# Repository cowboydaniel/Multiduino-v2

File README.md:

# Multiduino v2

**by Outback Electronics** — Arduino-Compatible Development Board

---

## Overview

The Multiduino v2 is an Arduino Uno-compatible development board designed for projects that need more than a standard Uno can offer. It uses the ATmega328PB processor and ATmega16U2 USB bridge — the same architecture as the official Arduino Uno R3, with a drop-in compatible (but enhanced) variant of the Uno's ATmega328P.

On top of the standard Uno feature set, the Multiduino v2 adds a substantial suite of on-board hardware: extra RAM and non-volatile storage, a precision real-time clock, a humidity and temperature sensor, a microSD card slot, and a switchable 3.3V power rail. Everything is ready to use without any external modules or wiring.

**Two ways to use this board:**

**Arduino Uno compatible mode** — Select **Arduino Uno** as your board in the Arduino IDE and the Multiduino v2 works immediately with standard Arduino libraries. This is the quickest way to get started and is fully supported. Compatible libraries for all on-board peripherals are available through the Arduino Library Manager.

**Multiduino core** — Outback Electronics provides a custom Arduino core specifically designed for this board. It includes tailored libraries for every on-board peripheral that expose hardware-specific functionality not possible with generic libraries. The Multiduino core is recommended for any project making full use of the board's hardware. See the [Multiduino Core repository](https://github.com/cowboydaniel/outback-arduino-avr) for installation instructions.

---

## What's On The Board

### Processor
The ATmega328PB is an enhanced version of the ATmega328P found in the official Arduino Uno R3. It is fully backward compatible with existing Arduino sketches and libraries. Compared to the 328P it adds additional timer/counters (providing more PWM channels), and four extra I/O pins (PE0–PE3) which are broken out on the extended header. The chip also includes a second USART, SPI, and I2C port internally, however these are not broken out on this board.

### Memory
Beyond the processor's built-in 2KB of RAM and 1KB of EEPROM, the Multiduino v2 includes three additional memory devices:

**2 Megabit SPI SRAM** — 256KB of fast external RAM accessible over SPI. Ideal for buffering large datasets, audio samples, or any data that is too large to fit in the processor's internal memory but does not need to survive a power cycle.

**64 Kilobit FRAM** — 8KB of non-volatile ferroelectric RAM. Unlike flash or EEPROM, FRAM can be written an effectively unlimited number of times (100 trillion write cycles) with no wear. Use it for variables, counters, or settings that change frequently and must be preserved across power cycles.

**32 Kilobit EEPROM with Unique Serial Number** — 4KB of standard I2C EEPROM. This chip also contains a factory-programmed 64-bit unique serial number, which can be read by your sketch and used to uniquely identify each individual board — useful for licensing, fleet management, or asset tracking.

### MicroSD Card Slot
A full-size microSD card slot (supports up to 32GB, FAT32 formatted) provides essentially unlimited storage for data logging, configuration files, audio, images, or any other file-based data. The SD card interface can be completely isolated from the SPI bus using the on-board slide switch, which is useful when no SD card is installed or when SPI bus conflicts need to be avoided.

### Real-Time Clock
The DS3231 is a high-precision, temperature-compensated real-time clock accurate to ±5 parts per million — less than half a second of drift per day — and requires no external crystal. It maintains the current date and time even when the board is powered off, provided a backup battery is connected to the on-board JST connector. A standard CR2032 coin cell in an appropriate holder, or a small LiPo battery, can be used for backup power.

### Humidity and Temperature Sensor
The SHT4x sensor measures ambient relative humidity (±1.8% accuracy) and temperature (±0.2°C accuracy) directly on the board. It communicates over I2C and is ready to use with no additional components.

### USB-C Connector
The board connects to your computer via USB-C for programming and serial communication, matching the same workflow as the Arduino Uno. The USB-C port is USB 2.0 and works with any standard USB-C cable.

---

## Pinout and Headers

The Multiduino v2 uses standard Arduino Uno-compatible headers, so Arduino shields and accessories are physically and electrically compatible.

**Digital I/O (IO0–IO7)** — 8 digital pins compatible with standard Arduino digital pins 0–7. IO0 and IO1 are the hardware serial port (RX/TX), also used during USB programming.

**Analog Inputs (A0–A5)** — 6 analog input pins compatible with standard Arduino analog pins. A4 and A5 are also the hardware I2C bus (SDA/SCL).

**SPI and Utility Header** — a 10-pin header exposing the SPI bus (SCK, MOSI, MISO), the dedicated SRAM chip select, the SD card chip select, I2C (SDA/SCL), the SD card detect signal, and AREF.

**Extended Pins (PE0–PE3)** — four additional I/O pins from the ATmega328PB's extended port, not present on a standard Uno. These can be used as general-purpose I/O or connected to on-board peripherals via solder jumpers (see the Solder Jumpers section).

**Power Header** — exposes 5V, raw input voltage, reset, and GND.

**ICSP Headers** — two standard 6-pin ICSP headers for programming the main processor and the USB bridge chip directly, without going through the bootloader.

---

## On-Board I2C Devices

All on-board I2C devices have unique addresses and none conflict with each other, leaving the bus free for additional external devices.

| Device | Address |
|--------|---------|
| SHT4x humidity/temperature sensor | 0x44 |
| EEPROM data | 0x50 |
| EEPROM serial number (read-only) | 0x58 |
| FRAM | 0x57 |
| DS3231 real-time clock | 0x68 |

The board uses a dual-voltage I2C architecture. The processor communicates at 5V, while the FRAM and temperature sensor operate at 3.3V. An on-board level translator bridges the two voltage domains transparently — your sketch communicates with all devices the same way regardless of their operating voltage.

---

## Slide Switch — SD Card Enable

The slide switch on the board enables or disables the microSD card interface.

- **ON** — the SD card is connected to the SPI bus and ready to use.
- **OFF** — the SD card is completely isolated from the SPI bus. Use this position when no SD card is installed, or if you need to ensure the SPI bus is unaffected by the SD card slot.

The 256KB SRAM is unaffected by the slide switch and is always accessible regardless of its position.

---

## Solder Jumpers

The board includes solder jumpers for configuring on-board hardware. These are small pads on the PCB. A jumper is **closed** by bridging the pads with a blob of solder, and **opened** by carefully cutting the trace between them with a sharp knife.

---

### JP2 — Auto-Reset

Controls whether the Arduino IDE can automatically reset the board to enter the bootloader when uploading a sketch.

| State | Behaviour |
|-------|-----------|
| **Closed** *(default)* | Auto-reset enabled. The IDE resets the board automatically at the start of each upload — no manual button press needed. |
| **Open** | Auto-reset disabled. You must manually press the reset button at the correct moment during upload, or use ICSP programming instead. |

Cut this jumper if you have an external device connected to the serial port that interferes with the reset pulse, or if you simply want to prevent accidental resets during upload.

---

### JP3 — PE0 / 32KHz RTC Output

Routes the real-time clock's 32KHz square wave output to the extended pin PE0.

| State | Behaviour |
|-------|-----------|
| **Open** *(default)* | PE0 is a free general-purpose I/O pin on the extended header. |
| **Closed** | The RTC's 32KHz output is connected to PE0. Configure PE0 as an **input** in your sketch. |

The 32KHz output can be used as an external clock source or timing reference. Do not configure PE0 as an output when this jumper is closed.

---

### JP4 — PE1 / RTC Alarm Interrupt

Routes the real-time clock's alarm interrupt and configurable square wave output to the extended pin PE1.

| State | Behaviour |
|-------|-----------|
| **Open** *(default)* | PE1 is a free general-purpose I/O pin on the extended header. |
| **Closed** | The RTC's SQW/INT output is connected to PE1. Configure PE1 as an **input** in your sketch. |

Via software this output can be set to generate a square wave (1Hz, 1.024kHz, 4.096kHz, or 8.192kHz) or to fire an interrupt when an RTC alarm triggers, enabling accurate wake-from-sleep functionality. Do not configure PE1 as an output when this jumper is closed.

---

### JP5 — PE2 / SD Card Switch State

Connects the extended pin PE2 to the same signal that controls the SD card slide switch, giving your sketch visibility into — and optionally control over — the SD card enable state.

| Position | Behaviour |
|----------|-----------|
| **Open** *(default)* | PE2 is a free general-purpose I/O pin. |
| **Closed** | PE2 is connected to the SD card enable line. |

**With JP5 closed, PE2 can be used in two ways:**

**As an input (read the switch state):** PE2 reads LOW when the slide switch is ON and the SD card is active, and HIGH when the switch is OFF and the SD card is disabled. This lets your sketch detect whether the SD card is enabled before attempting to use it.

**As an output (software control of the SD card):** With the slide switch in the OFF position, driving PE2 LOW in your sketch will enable the SD card — exactly as if the switch were turned on. Driving PE2 HIGH will keep the SD card disabled. This allows full software control of the SD card without touching the physical switch.

> **Warning:** If the slide switch is in the ON position, do not configure PE2 as an output. The switch holds the enable line LOW directly, and driving PE2 HIGH against it will cause a conflict between the MCU output and the switch. Always ensure the slide switch is OFF before using PE2 as an output to control the SD card.

---

### JP6 — PE3 Routing

JP6 is a two-position jumper that determines where the extended pin PE3 is connected. It works in conjunction with JP7 to configure 3.3V rail control.

| Position | Behaviour |
|----------|-----------|
| **A–C** *(default)* | PE3 is connected to the 3.3V rail enable line. Combined with JP7 in its default position, your sketch can drive PE3 HIGH to turn the 3.3V rail on, or LOW to turn it off. |
| **B–C** | PE3 is routed out to the extended header (pin 4) as a free general-purpose I/O pin, and has no connection to the 3.3V enable circuit. |

---

### JP7 — 3.3V Rail Enable Source

JP7 is a two-position jumper that determines what controls the 3.3V power rail enable line. It should be configured in conjunction with JP6.

| Position | Behaviour |
|----------|-----------|
| **A–C** *(default)* | The 3.3V rail enable line is connected to PE3 (via JP6). The rail defaults to **off** at power-up and is controlled by your sketch via PE3. |
| **B–C** | The 3.3V rail enable line is connected directly to +5V. The rail is **always on** as soon as the board is powered, regardless of JP6 or PE3. |

**Combined JP6 + JP7 configuration options:**

| JP7 | JP6 | Result |
|-----|-----|--------|
| **A–C** + **A–C** | MCU PE3 → EN line | 3.3V rail controlled by sketch. Drive PE3 HIGH to enable, LOW to disable. Rail defaults off at power-up. |
| **A–C** + **B–C** | PE3 routed to header, EN line floating | 3.3V rail stays **off** permanently. Use only if 3.3V devices are not needed. |
| **B–C** + any | +5V → EN line | 3.3V rail **always on** at power-up. PE3 is free for other use. |

> **Important:** In the default configuration (both jumpers A–C), the FRAM, temperature sensor, and SD card are all off until your sketch drives PE3 HIGH. If your project needs these devices available immediately at power-up — for example if you access the SD card before your sketch has had a chance to run — move JP7 to the B–C position instead.

Turning off the 3.3V rail via software powers down the FRAM, temperature sensor, and SD card simultaneously, which can significantly reduce power consumption during sleep or idle periods.

---

## LEDs

| LED | Colour | Function |
|-----|--------|----------|
| Power | Green | Lit whenever the board is powered |
| Pin 13 | Yellow | Connected to digital pin 13. Blinks during SPI communication and can be controlled with `digitalWrite(13, ...)` |
| RX | Yellow | Flashes when the board receives data over USB serial |
| TX | Yellow | Flashes when the board transmits data over USB serial |

---

## Power

The board is powered via the USB-C connector. The 5V rail supplies the processor and all 5V peripherals. The 3.3V rail powers the FRAM, temperature sensor, and SD card, and is controlled by the JP7 jumper setting.

A self-resetting polyfuse protects the USB power input against overcurrent faults and resets automatically once the fault clears.

**Approximate current consumption:**

| Condition | Current |
|-----------|---------|
| Idle, no SD card activity | ~95 mA |
| Active with SD card writing | ~345 mA peak |

The board draws well within the 500mA USB specification under normal operation.

---

## Getting Started

### Option 1 — Arduino Uno Compatible Mode

The quickest way to get up and running. No custom core installation required.

1. Install the [Arduino IDE](https://www.arduino.cc/en/software) if not already installed.
2. Connect the Multiduino v2 to your computer with a USB-C cable.
3. In the Arduino IDE, select **Tools → Board → Arduino Uno**.
4. Select the correct port under **Tools → Port**.
5. Open any sketch and click **Upload**.

For the on-board peripherals, use the standard Arduino Wire and SPI libraries. Compatible libraries for the DS3231, SHT4x, FRAM, and EEPROM are available through the Arduino Library Manager.

### Option 2 — Multiduino Core (Recommended)

The Multiduino core unlocks the full capability of the board's hardware with libraries written specifically for it. Features like software SD card control, 3.3V rail switching, and board-aware peripheral management are only available through the core.

1. Install the [Arduino IDE](https://www.arduino.cc/en/software) if not already installed.
2. Follow the installation instructions in the [Multiduino Core repository](https://github.com/cowboydaniel/outback-arduino-avr) to add the board to the IDE.
3. Select **Tools → Board → Multiduino v2**.
4. Connect via USB-C, select the correct port, and upload as normal.

All standard Arduino sketches remain compatible when using the Multiduino core.

---

## RTC Battery Backup

To retain the time and date when the board is powered off, connect a backup battery to the JST 1.00mm 2-pin connector. A CR2032 coin cell in a compatible JST-terminated holder (3V) is recommended. The RTC draws only a few microamps from the backup supply, so a single CR2032 will last several years.

---

*Multiduino v2 — Outback Electronics*

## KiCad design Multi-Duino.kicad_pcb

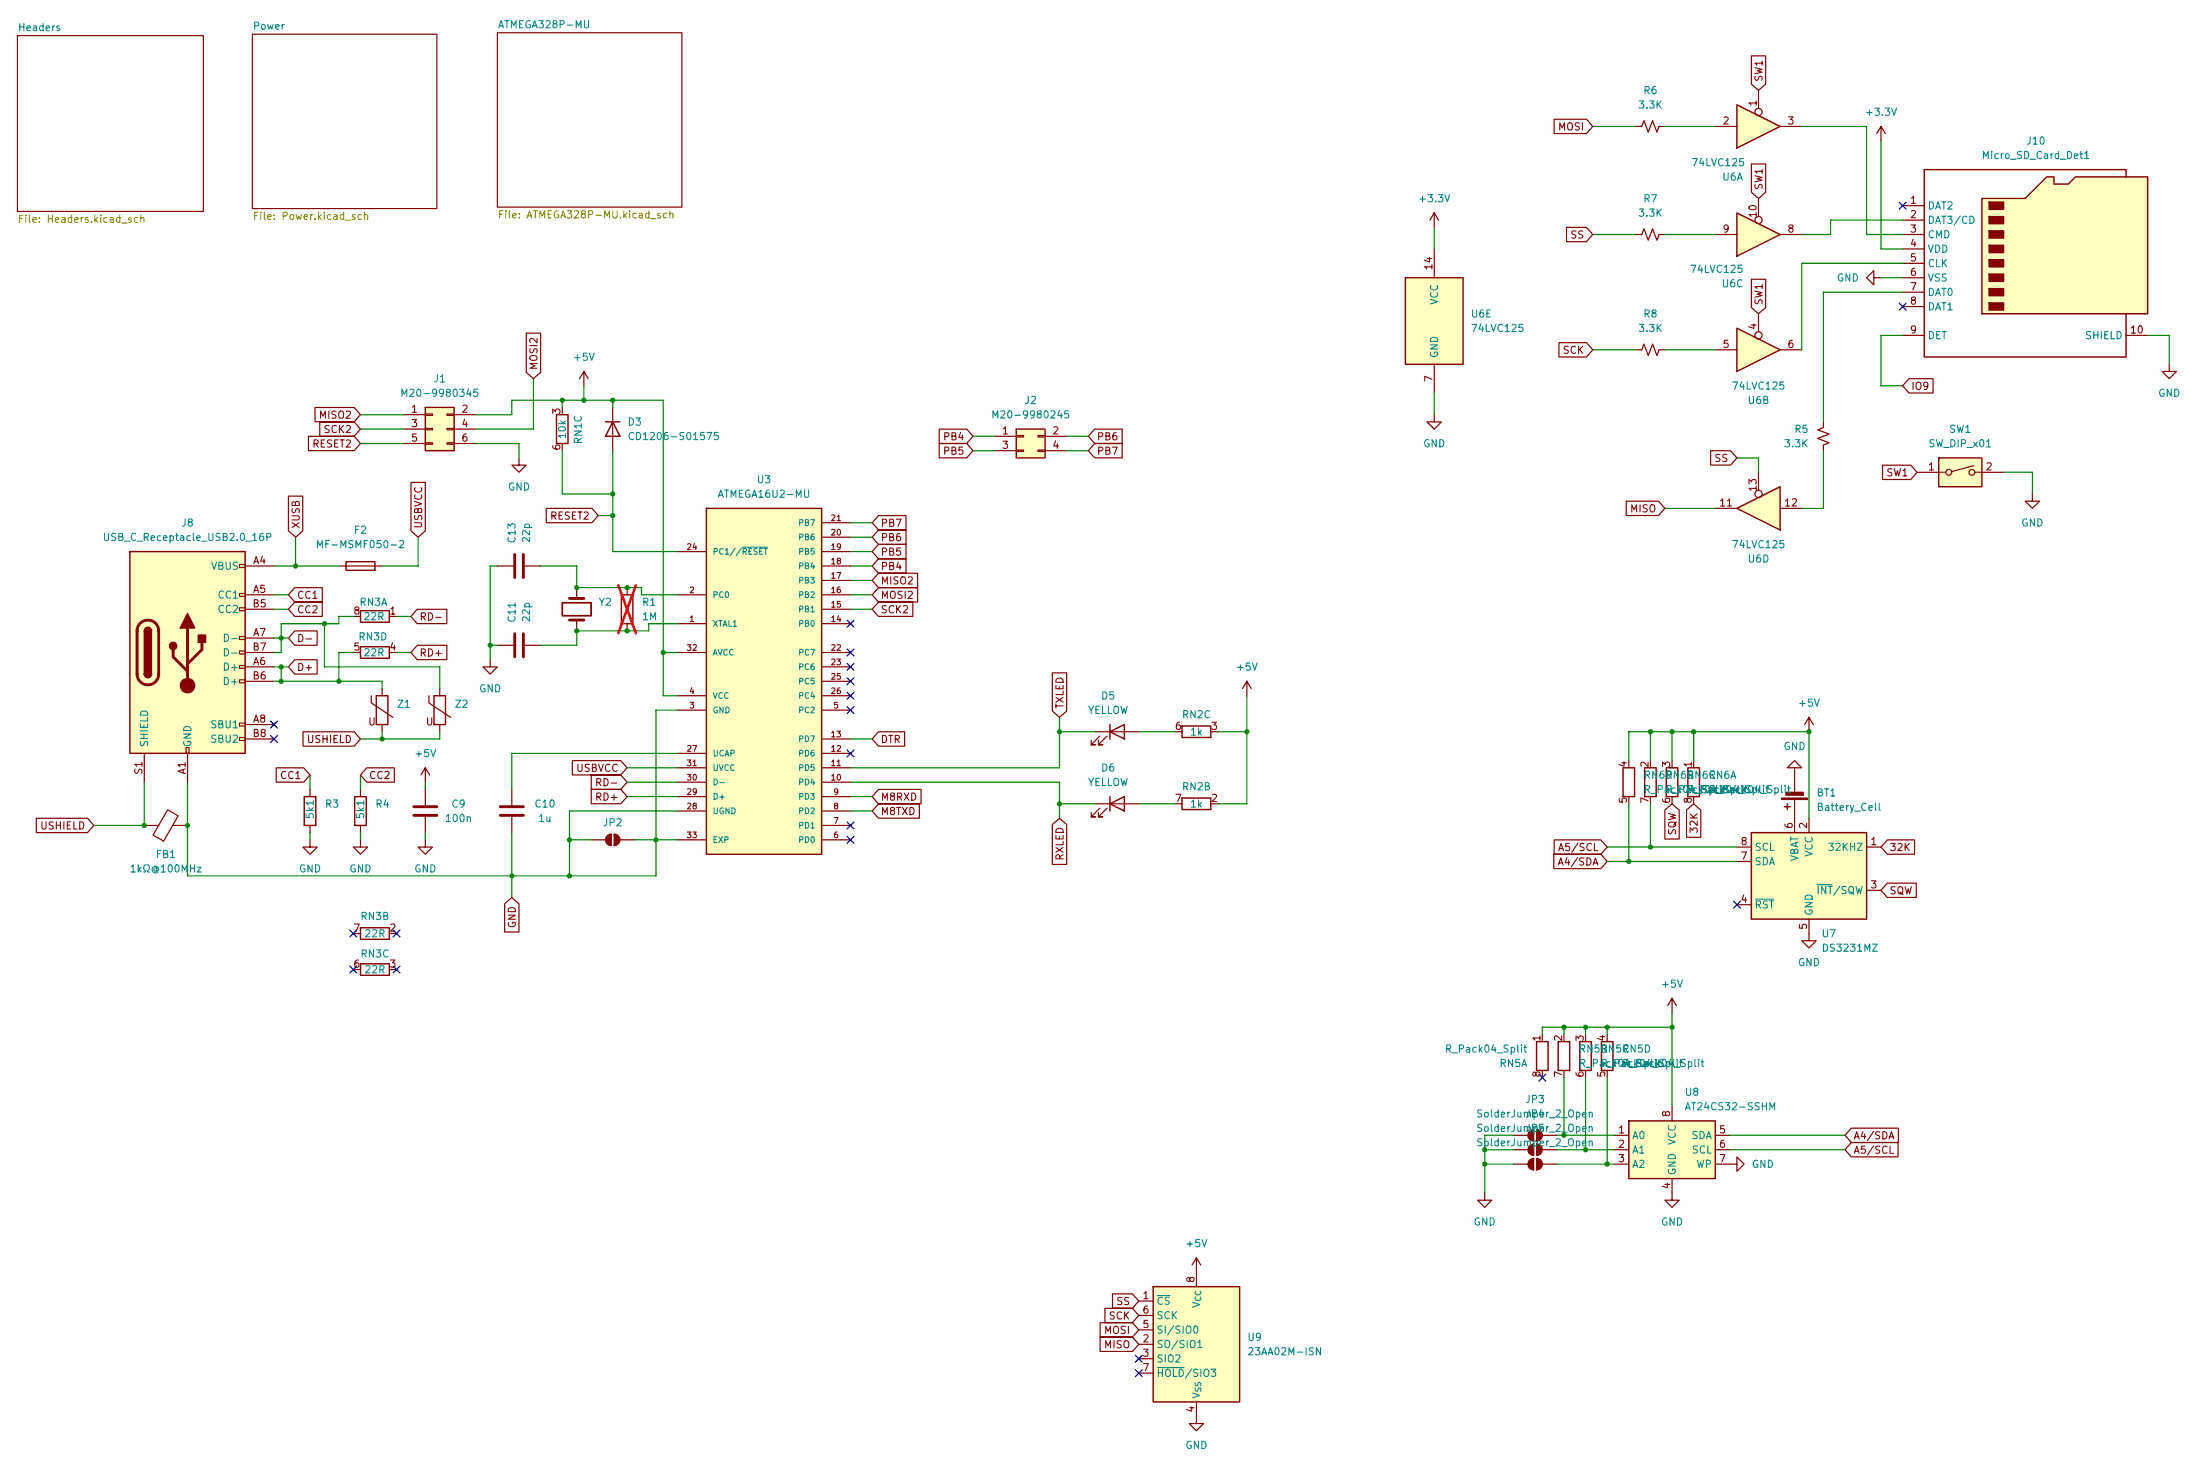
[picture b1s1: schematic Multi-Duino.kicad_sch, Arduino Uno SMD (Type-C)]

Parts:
BT1: Battery_Cell; Battery_Panasonic_CR2032-HFN_Horizontal_CircularHoles
C9: 100n; C_0603_1608Metric
C10: 1u; C_0603_1608Metric
C11, C13: 22p; C_0603_1608Metric
D3: CD1206-S01575; D_1206_3216Metric
D5, D6: YELLOW; LED_0805_2012Metric
F2: MF-MSMF050-2; Fuse_1812_4532Metric_Pad1.30x3.40mm_HandSolder
FB1: 1kΩ@100MHz; L_0805_2012Metric
J1: M20-9980345; PinHeader_2x03_P2.54mm_Vertical
J2: M20-9980245; CONN_M20-9980245_HRW
J8: USB_C_Receptacle_USB2.0_16P; USB_C_Receptacle_GCT_USB4105-xx-A_16P_TopMnt_Horizontal
J10: Micro_SD_Card_Det1; microSD_HC_Hirose_DM3D-SF
JP2, JP3, JP4, JP5: SolderJumper_2_Open; SolderJumper-2_P1.3mm_Open_Pad1.0x1.5mm
R1: 1M; R_0603_1608Metric; not fitted
R3, R4: 5k1; R_0603_1608Metric
R5, R6, R7, R8: 3.3K; R_0201_0603Metric
RN1: 10k; R_Array_Convex_4x0603
RN2: 1k; R_Array_Convex_4x0603
RN3: 22R; R_Array_Convex_4x0603
RN5, RN6: R_Pack04_Split; R_Array_Convex_4x0603
SW1: SW_DIP_x01; SW_DIP_SPSTx01_Slide_6.7x4.1mm_W6.73mm_P2.54mm_LowProfile_J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
U3: ATMEGA16U2-MU; VQFN-32-1EP_5x5mm_P0.5mm_EP3.1x3.1mm
U6: 74LVC125; TSSOP-14_4.4x5mm_P0.65mm
U7: DS3231MZ; SOIC-8_3.9x4.9mm_P1.27mm
U8: AT24CS32-SSHM; SOIC-8_3.9x4.9mm_P1.27mm
U9: 23AA02M-ISN; SOIC-8_3.9x4.9mm_P1.27mm
Y2: LFXTAL003240BULK; Crystal_HC49-4H_Vertical
Z1, Z2: 5pF@1MHz; R_0603_1608Metric

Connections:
32K: RN6.8 (R1.2), U7.1 (32KHZ)
+3.3V: J10.4 (VDD), U6.14 (VCC); also elsewhere on the board
+5V: C9.1, D3.1 (K), J1.2, RN1.3 (R3.1), RN2.2 (R2.1), RN2.3 (R3.1), RN5.1 (R1.1), RN5.2 (R2.1), RN5.3 (R3.1), RN5.4 (R4.1), RN6.1 (R1.1), RN6.2 (R2.1), RN6.3 (R3.1), RN6.4 (R4.1), U3.4 (VCC), U3.32 (AVCC), U7.2 (VCC), U8.8 (VCC), U9.8 (V_{CC}); also elsewhere on the board
A4/SDA: RN6.5 (R4.2), U7.7 (SDA), U8.5 (SDA); also elsewhere on the board
A5/SCL: RN6.7 (R2.2), U7.8 (SCL), U8.6 (SCL); also elsewhere on the board
CC1: J8.A5 (CC1), R3.1
CC2: J8.B5 (CC2), R4.1
D+: J8.A6 (D+), J8.B6 (D+), RN3.5 (R4.2), Z1.1
D-: J8.A7 (D-), J8.B7 (D-), RN3.8 (R1.2), Z2.1
DTR: U3.13 (PD7); also elsewhere on the board
GND: BT1.2 (-), C9.2, C10.1, C11.2, C13.2, FB1.2, J1.6, J8.A1 (GND), J8.A12 (GND), J8.B1 (GND), J8.B12 (GND), J10.6 (VSS), J10.10 (SHIELD), JP2.1 (A), JP2.2 (B), JP3.1 (A), JP4.1 (A), JP5.1 (A), R3.2, R4.2, SW1.2, U3.3 (GND), U3.28 (UGND), U3.33 (EXP), U6.7 (GND), U7.5 (GND), U8.4 (GND), U8.7 (WP), U9.4 (V_{SS}); also elsewhere on the board
IO9: J10.9 (DET); also elsewhere on the board
M8RXD: U3.9 (PD3); also elsewhere on the board
M8TXD: U3.8 (PD2); also elsewhere on the board
MISO: U6.11, U9.2 (SO/SIO1); also elsewhere on the board
MISO2: J1.1, U3.17 (PB3)
MOSI: R6.1, U9.5 (SI/SIO0); also elsewhere on the board
MOSI2: J1.4, U3.16 (PB2)
unnamed: BT1.1 (+), U7.6 (VBAT)
unnamed: D5.2 (A), RN2.6 (R3.2)
unnamed: D6.2 (A), RN2.7 (R2.2)
unnamed: J10.5 (CLK), U6.6
unnamed: J10.3 (CMD), U6.3
unnamed: J10.7 (DAT0), R5.1
unnamed: J10.2 (DAT3/CD), U6.8
unnamed: JP3.2 (B), RN5.7 (R2.2), U8.1 (A0)
unnamed: JP4.2 (B), RN5.6 (R3.2), U8.2 (A1)
unnamed: JP5.2 (B), RN5.5 (R4.2), U8.3 (A2)
unnamed: R5.2, U6.12
unnamed: R6.2, U6.2
unnamed: R7.2, U6.9
unnamed: R8.2, U6.5
unnamed: C13.1, R1.1, U3.2 (PC0), Y2.1
unnamed: C10.2, U3.27 (UCAP)
unnamed: C11.1, R1.2, U3.1 (XTAL1), Y2.2
PB4: J2.1, U3.18 (PB4)
PB5: J2.3, U3.19 (PB5)
PB6: J2.2, U3.20 (PB6)
PB7: J2.4, U3.21 (PB7)
RD+: RN3.4 (R4.1), U3.29 (D+)
RD-: RN3.1 (R1.1), U3.30 (D-)
RESET2: D3.2 (A), J1.5, RN1.6 (R3.2), U3.24 (PC1//~RESET)
RXLED: D6.1 (K), U3.10 (PD4)
SCK: R8.1, U9.6 (SCK); also elsewhere on the board
SCK2: J1.3, U3.15 (PB1)
SQW: RN6.6 (R3.2), U7.3 (~INT/SQW)
SS: R7.1, U6.13, U9.1 (~CS); also elsewhere on the board
SW1: SW1.1, U6.1, U6.4, U6.10
TXLED: D5.1 (K), U3.11 (PD5)
USBVCC: F2.2, U3.31 (UVCC); also elsewhere on the board
USHIELD: FB1.1, J8.S1 (SHIELD), Z1.2, Z2.2
XUSB: F2.1, J8.A4 (VBUS), J8.A9 (VBUS), J8.B4 (VBUS), J8.B9 (VBUS)

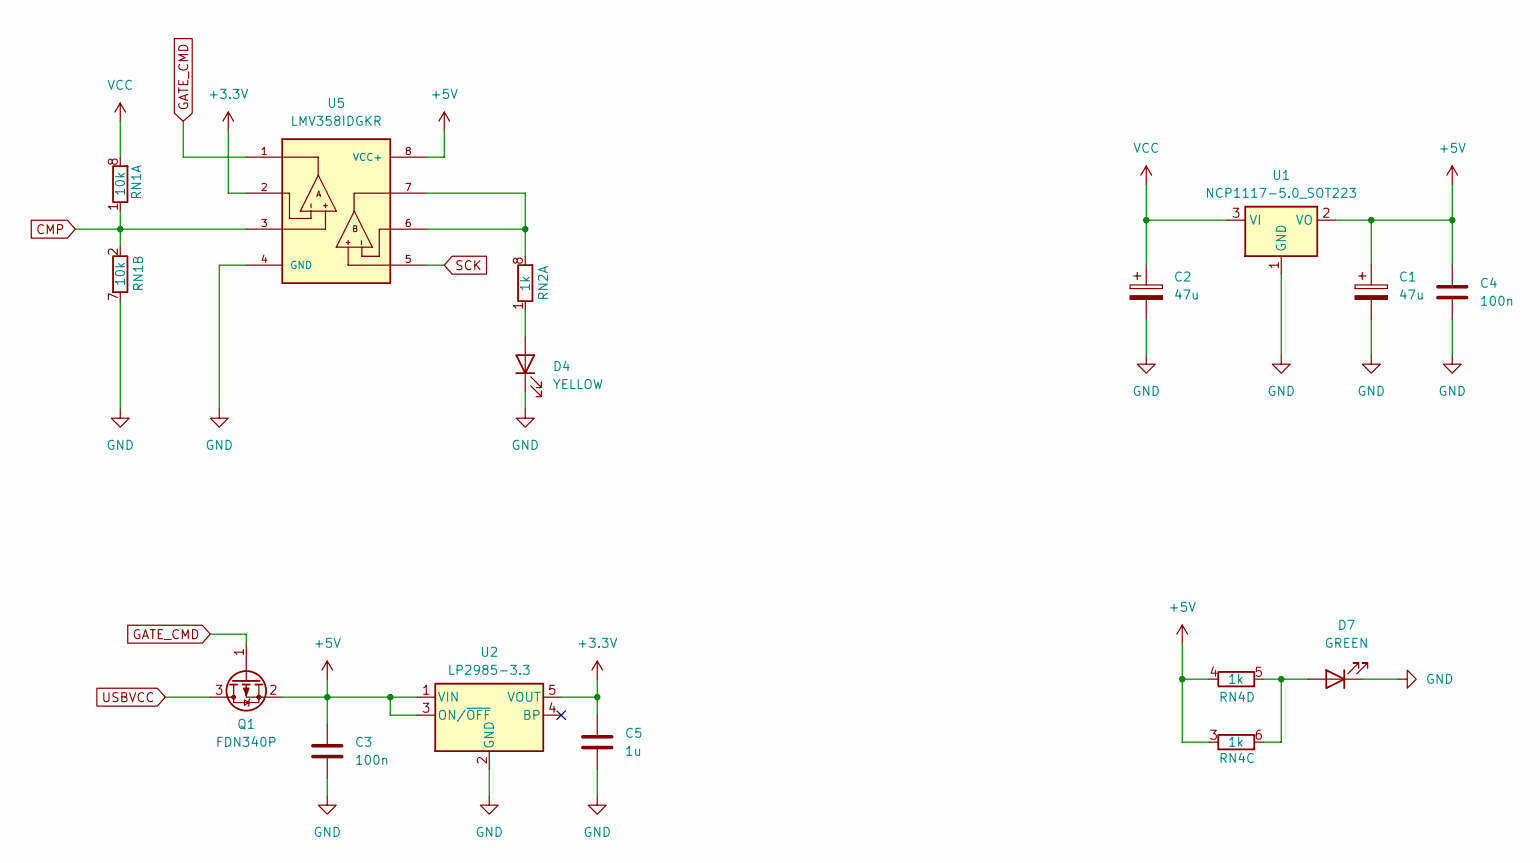
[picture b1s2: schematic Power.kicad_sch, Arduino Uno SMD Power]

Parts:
C1, C2: 47u; CAP_EEHZA1E470P
C3, C4: 100n; C_0603_1608Metric
C5: 1u; C_0603_1608Metric
D4: YELLOW; LED_0805_2012Metric
D7: GREEN; LED_0805_2012Metric
Q1: FDN340P; SC-59
RN1: 10k; R_Array_Convex_4x0603
RN2, RN4: 1k; R_Array_Convex_4x0603
U1: NCP1117-5.0_SOT223; SOT-223-3_TabPin2
U2: LP2985-3.3; SOT-23-5
U5: LMV358IDGKR; MSOP-8_3x3mm_P0.65mm; PARTREV X

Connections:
+3.3V: C5.2, U2.5 (VOUT), U5.2; also elsewhere on the board
+5V: C1.1, C3.2, C4.1, Q1.2 (S), RN4.3 (R3.1), RN4.4 (R4.1), U1.2 (VO), U2.1 (VIN), U2.3 (ON/~OFF), U5.8 (VCC+); also elsewhere on the board
CMP: RN1.1 (R1.1), RN1.2 (R2.1), U5.3
GATE_CMD: Q1.1 (G), U5.1
GND: C1.2, C2.2, C3.1, C4.2, C5.1, D4.1 (K), D7.1 (K), RN1.7 (R2.2), U1.1 (GND), U2.2 (GND), U5.4 (GND); also elsewhere on the board
unnamed: D4.2 (A), RN2.1 (R1.1)
unnamed: D7.2 (A), RN4.5 (R4.2), RN4.6 (R3.2)
unnamed: RN2.8 (R1.2), U5.6, U5.7
SCK: U5.5; also elsewhere on the board
USBVCC: Q1.3 (D); also elsewhere on the board
VCC: C2.1, RN1.8 (R1.2), U1.3 (VI); also elsewhere on the board

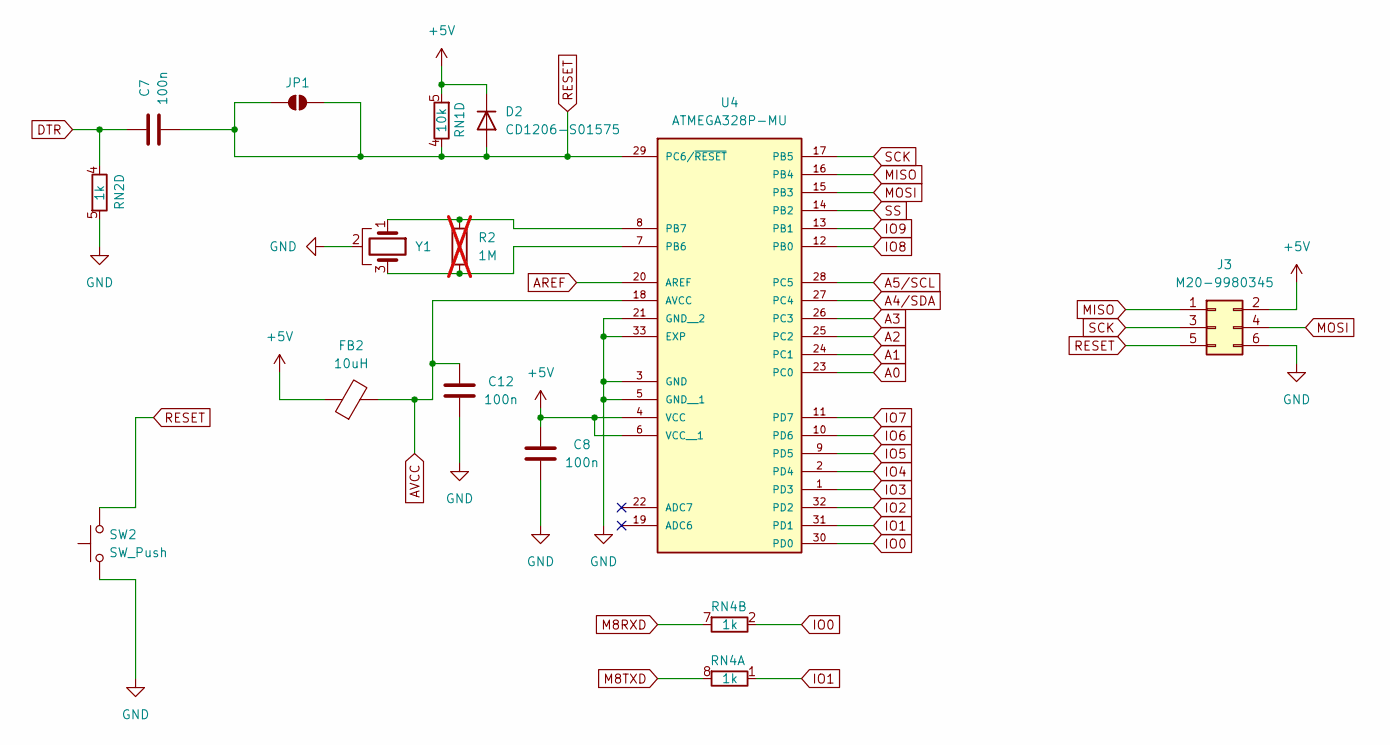
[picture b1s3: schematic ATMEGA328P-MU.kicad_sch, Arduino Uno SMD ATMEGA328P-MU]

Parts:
C7, C8, C12: 100n; C_0603_1608Metric
D2: CD1206-S01575; D_1206_3216Metric
FB2: 10uH; L_0805_2012Metric
J3: M20-9980345; PinHeader_2x03_P2.54mm_Vertical
JP1: SolderJumper_2_Open; SolderJumper-2_P1.3mm_Open_Pad1.0x1.5mm
R2: 1M; R_0603_1608Metric; not fitted
RN1: 10k; R_Array_Convex_4x0603
RN2, RN4: 1k; R_Array_Convex_4x0603
SW2: SW_Push; SW_Push_1P1T_NO_CK_KSC6xxJ
U4: ATMEGA328P-MU; VQFN-32-1EP_5x5mm_P0.5mm_EP3.1x3.1mm
Y1: CSTNE16M0V530000R0; Resonator_SMD_Murata_CSTxExxV-3Pin_3.0x1.1mm

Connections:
+5V: C8.2, D2.1 (K), FB2.1, J3.2, RN1.5 (R4.2), U4.4 (VCC), U4.6 (VCC__1); also elsewhere on the board
A0: U4.23 (PC0); also elsewhere on the board
A1: U4.24 (PC1); also elsewhere on the board
A2: U4.25 (PC2); also elsewhere on the board
A3: U4.26 (PC3); also elsewhere on the board
A4/SDA: U4.27 (PC4); also elsewhere on the board
A5/SCL: U4.28 (PC5); also elsewhere on the board
AREF: U4.20 (AREF); also elsewhere on the board
AVCC: C12.1, FB2.2, U4.18 (AVCC)
DTR: C7.1, RN2.4 (R4.1); also elsewhere on the board
GND: C8.1, C12.2, J3.6, RN2.5 (R4.2), SW2.1, U4.3 (GND), U4.5 (GND__1), U4.21 (GND__2), U4.33 (EXP), Y1.2; also elsewhere on the board
IO0: RN4.2 (R2.1), U4.30 (PD0); also elsewhere on the board
IO1: RN4.1 (R1.1), U4.31 (PD1); also elsewhere on the board
IO2: U4.32 (PD2); also elsewhere on the board
IO3: U4.1 (PD3); also elsewhere on the board
IO4: U4.2 (PD4); also elsewhere on the board
IO5: U4.9 (PD5); also elsewhere on the board
IO6: U4.10 (PD6); also elsewhere on the board
IO7: U4.11 (PD7); also elsewhere on the board
IO8: U4.12 (PB0); also elsewhere on the board
IO9: U4.13 (PB1); also elsewhere on the board
M8RXD: RN4.7 (R2.2); also elsewhere on the board
M8TXD: RN4.8 (R1.2); also elsewhere on the board
MISO: J3.1, U4.16 (PB4); also elsewhere on the board
MOSI: J3.4, U4.15 (PB3); also elsewhere on the board
unnamed: R2.2, U4.7 (PB6), Y1.3
unnamed: R2.1, U4.8 (PB7), Y1.1
RESET: C7.2, D2.2 (A), J3.5, JP1.1 (A), JP1.2 (B), RN1.4 (R4.1), SW2.2, U4.29 (PC6/~RESET); also elsewhere on the board
SCK: J3.3, U4.17 (PB5); also elsewhere on the board
SS: U4.14 (PB2); also elsewhere on the board

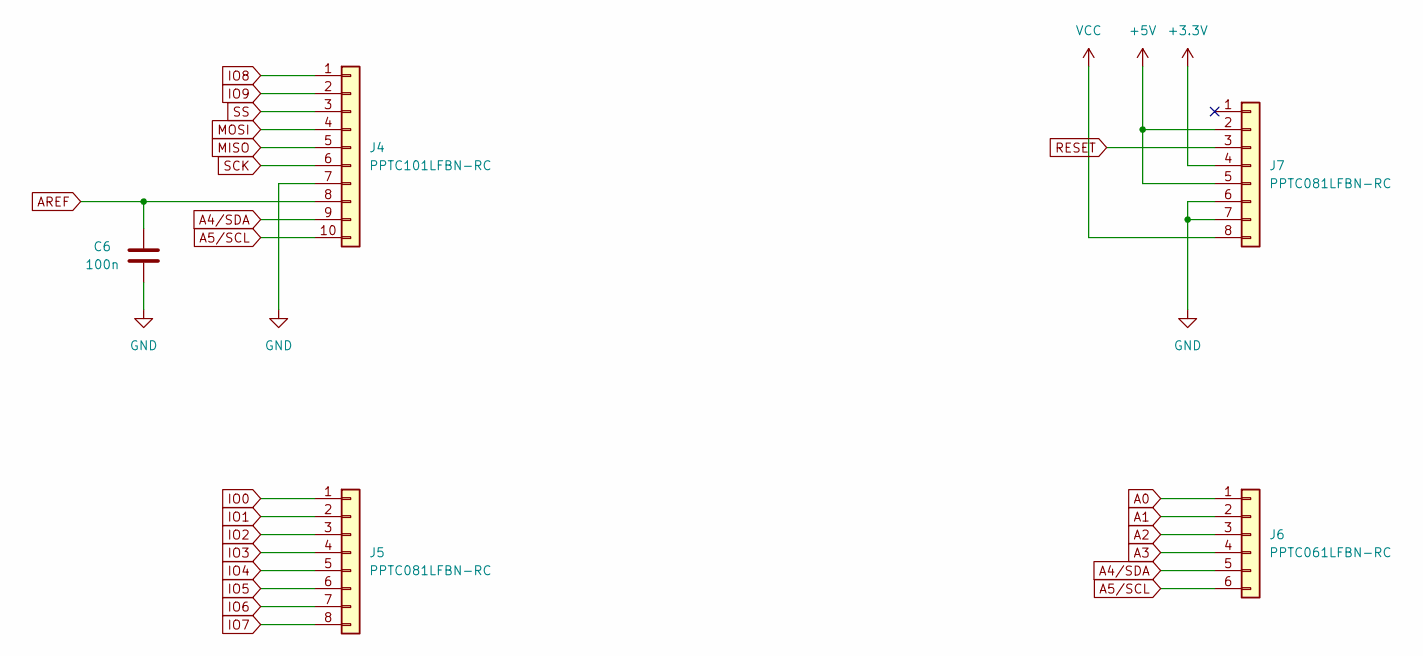
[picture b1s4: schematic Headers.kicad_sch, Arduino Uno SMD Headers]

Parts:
C6: 100n; C_0603_1608Metric
J4: PPTC101LFBN-RC; PinSocket_1x10_P2.54mm_Vertical
J5, J7: PPTC081LFBN-RC; PinSocket_1x08_P2.54mm_Vertical
J6: PPTC061LFBN-RC; PinSocket_1x06_P2.54mm_Vertical

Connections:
+3.3V: J7.4; also elsewhere on the board
+5V: J7.2, J7.5; also elsewhere on the board
A0: J6.1; also elsewhere on the board
A1: J6.2; also elsewhere on the board
A2: J6.3; also elsewhere on the board
A3: J6.4; also elsewhere on the board
A4/SDA: J4.9, J6.5; also elsewhere on the board
A5/SCL: J4.10, J6.6; also elsewhere on the board
AREF: C6.1, J4.8; also elsewhere on the board
GND: C6.2, J4.7, J7.6, J7.7; also elsewhere on the board
IO0: J5.1; also elsewhere on the board
IO1: J5.2; also elsewhere on the board
IO2: J5.3; also elsewhere on the board
IO3: J5.4; also elsewhere on the board
IO4: J5.5; also elsewhere on the board
IO5: J5.6; also elsewhere on the board
IO6: J5.7; also elsewhere on the board
IO7: J5.8; also elsewhere on the board
IO8: J4.1; also elsewhere on the board
IO9: J4.2; also elsewhere on the board
MISO: J4.5; also elsewhere on the board
MOSI: J4.4; also elsewhere on the board
RESET: J7.3; also elsewhere on the board
SCK: J4.6; also elsewhere on the board
SS: J4.3; also elsewhere on the board
VCC: J7.8; also elsewhere on the board

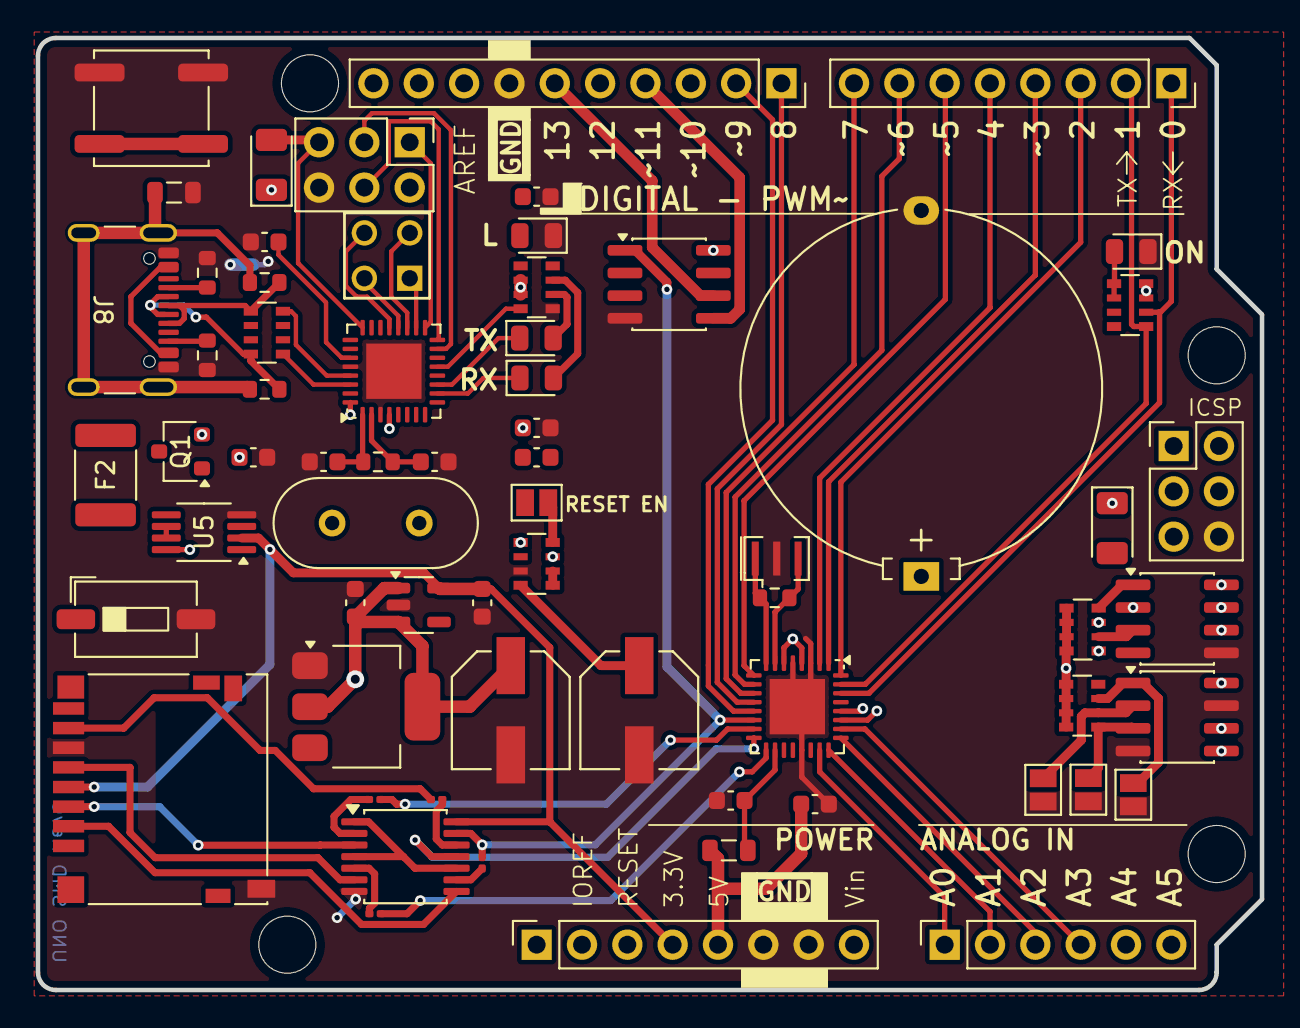
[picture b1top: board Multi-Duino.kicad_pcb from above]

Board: 4 copper layers, 68.6 x 53.3 mm, 67 parts (1 on the bottom side), 76 nets.

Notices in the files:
Multiduino.kicad_pcb:
© 2026 Outback Electronics
